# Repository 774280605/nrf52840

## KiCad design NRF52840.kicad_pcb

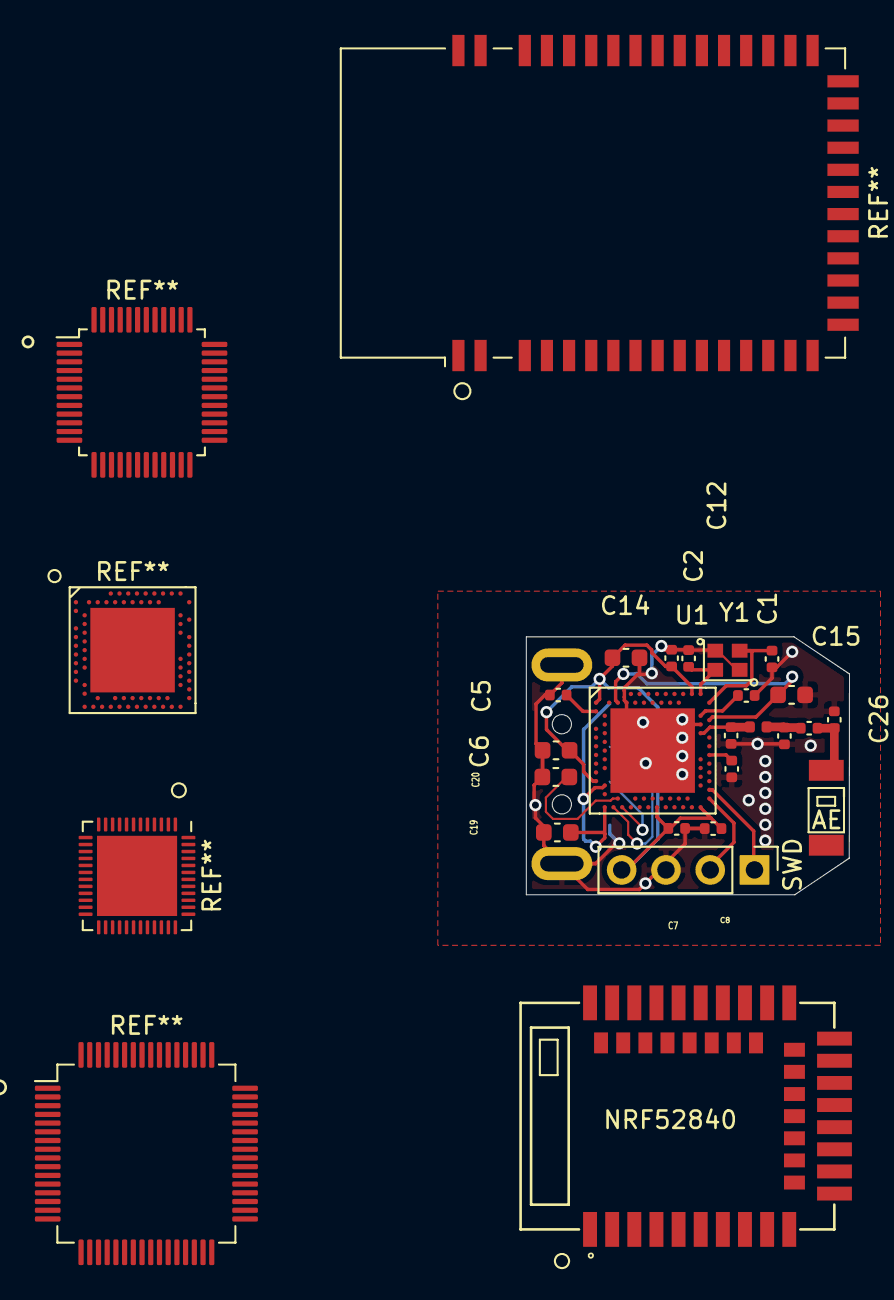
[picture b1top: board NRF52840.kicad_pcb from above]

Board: 2 copper layers, 24 parts (1 on the bottom side), 17 nets.

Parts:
AE: Antenna; 2.4g_ANTENNA
C1, C2: 12pF; C_0402_1005Metric
C3, C4: 1.0pF; C_0402_1005Metric
C5, C7: 100nf; C_0402_1005Metric
C6, C19, C20: 4.7uF; C_0603_1608Metric
C8, C12: 100nF; C_0402_1005Metric
C9: 820pF; C_0402_1005Metric
C11: 100pF; C_0402_1005Metric
C14, C15: 1.0uF; C_0603_1608Metric
C26: 1.5pF; C_0402_1005Metric
J2: USB_A; USB_A_CNCTech_1001-011-01101_Horizontal
L1: 3.9nH; L_0402_1005Metric
NRF52840: nrf52840_mode
R1: 0R; C_0402_1005Metric
SWD: Conn_01x04; PinHeader_1x04_P2.54mm_Vertical
U1: nRF52840; Nordic_AQFN-73-1EP_7x7mm_P0.5mm
Y1: 32M; Crystal_SMD_2016-4Pin_2.0x1.6mm

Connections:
+3V3: C6.1, C7.1, C8.1, C12.1, C14.1, SWD.4, U1.A22, U1.AD14, U1.AD23, U1.B1, U1.W1
+5V: C19.1, J2.1, U1.AD2, U1.Y2
D+: J2.3, U1.AD6
D-: J2.2, U1.AD4
GND: C1.1, C2.1, C3.1, C4.2, C5.2, C6.2, C7.2, C8.2, C9.2, C11.1, C12.2, C14.2, C15.2, C19.2, C20.2, C26.2, J2.4, J2.5, SWD.3, U1.B7, U1.EP, U1.F23, Y1.2, Y1.4
unnamed: AE.1, C26.1, R1.1
unnamed: C1.2, U1.B24, Y1.3
unnamed: C2.2, U1.A23, Y1.1
unnamed: C3.2, L1.2, U1.H23
unnamed: C4.1, L1.1, R1.2
unnamed: C5.1, U1.C1
unnamed: C9.1, U1.N24
unnamed: C11.2, U1.D23
unnamed: C15.1, U1.B5, U1.E24
unnamed: C20.1, U1.AC5
SWDCLK: SWD.1, U1.AA24
SWDIO: SWD.2, U1.AC24
